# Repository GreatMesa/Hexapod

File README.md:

# Arduino Servo-Powered Hexapod

This hexapod robot is a six-legged walking remote controlled robot that is designed for experimental and recreational purposes.

## Introduction
The 6 legs on the robot are designed to be as stable as possible, this means that the robot doesn't have to spend as much of its power in active stabilization. Besides that, the robot is also made with 3 degree of freedom, which not only model a normal leg of a anthropod but also designates a part of the leg for horizontal, vertical, and extensional movements respectfully. This gives the robot 18 degrees of freedom in total, allowing for more complex walking gait cycles and overall complex movements such as jumping, turning, and speed adjustments. With this alongside potential future sensor integration, I plan to make a robot that can effectively traverse the enviroment around it.

## Manufacturing / Parts (Mechanical Aspect)
For the mechanical aspect of this project I decided to split it into non-custom mechanical part selection, non-custom electrionics selection, custom part manufacturing, and bill of materials. This allows me to better explain each proccess instead of it being all lumped together.

### Non-Custom Mechanical Part Selection
For the servo motors, I want to use the DSServo 35KG servos due to their fast speed and high load tolerance. For the bearings (to reduce the friction on the legs) I utilized the MR148ZZ Deep Groove Ball Bearings due to how small yet efficient they were. For the screws, I selected M3 screws due to being the screw sizes that are standard for the servos I would be using while also being regularly used on 3D prints. Finally, the heated inserts I selected were the M3 3 * 4 * 5 inserts ude to interacting with the M3 screws.

### Non-Custom Electronics Selection
For the Arduino board, the only Arduino that had enough pins for what I wanted to accomplish was the Arduino Mega, although I am pondering a switch to the Arduino Mega Mini to have more space. For the wireless communication protocol I am using 2 NRF24L01+ modules. Besides these 2 sensors I also want to integrate sensors for the robot such as the MPU-6050, and for the RC Transceiver I plan to update this list with the according sensors.

### Custom Part Manufacturing
I plan to use Elegoo Plan PLUS to print out all the custom parts of the hexapod. This filament is good because it is inexpensive for how well it functions. Elegoo Pla Plus gives me the required strength I need for these parts while also allowing me to use a lower than normal infill percentage (15 %). I also plan to use 2 seperate colors (black and red) to not only distinguish between parts, but to also have a cool black spiderman color scheme.

# Component Purchase List

| Item Name | Price (USD) | Quantity | Total Price (USD) | Purchase Link |
|-----------|-------------|----------|--------------------|----------------|
| Dsservo 35KG DS3235 Metal Gear Digital Servo | $8.37 | 20 | $167.67 | [Alibaba](https://www.alibaba.com/product-detail/Dsservo-Waterproof-Servo-High-Torque-35KG_62204650069.html) |
| Chanzon Header Strip for Arduino GPIO 40-pin x 20pcs Female/Male Pins | $9.99 | 1 | $9.99 | [Amazon](https://www.amazon.com/gp/product/B09MY5MJ36) |
| HiLetgo 4pcs NRF24L01+ | $7.89 | 1 | $7.89 | [Amazon](https://www.amazon.com/gp/product/B00LX47OCY) |
| 1600 Pcs M3 Screw Kit, M3 Button Head and Socket Head Screws | $15.00 | 1 | $15.00 | [Amazon](https://www.amazon.com/Takytao-Button-Screws-Machine-Assortment/dp/B0D3TRRKSG) |
| SUNLU TPU 3D Printer Filament 1.75mm | $23.99 | 1 | $23.99 | [Amazon](https://www.amazon.com/SUNLU-TPU-Filament-1-75mm-Flexible/dp/B0BXNWK6NS) |
| ELEGOO PLA Plus Filament 1.75mm Red 1KG | $19.99 | 1 | $19.99 | [Amazon](https://www.amazon.com/ELEGOO-Filament-Dimensional-Accuracy-Compatible/dp/B0BM72LMQH) |
| ELEGOO PLA Plus Filament 1.75mm Black 1KG | $16.99 | 1 | $16.99 | [Amazon](https://www.amazon.com/ELEGOO-Filament-Dimensional-Accuracy-Compatible/dp/B0BM721XHT) |
| MEGA 2560 PRO Embed | $17.99 | 1 | $17.99 | [Amazon](https://www.amazon.com/Songhe-MEGA-2560-ATMEGA2560-Pro-Pinheader/dp/B07TGF9VMQ) |
| BOJACK 3 Values 130 Pcs Solderless Breadboard | $9.99 | 1 | $9.99 | [Amazon](https://www.amazon.com/BOJACK-Values-Solderless-Breadboard-Flexible/dp/B08Y59P6D1) |
| 24 Values Electrolytic Capacitor Assortment Kit | $9.99 | 1 | $9.99 | [Amazon](https://www.amazon.com/ALLECIN-Electrolytic-Capacitor-Assortment-Kit/dp/B0C1VBXCQM) |
| QTEATAK 2Pcs AC 20A/125V 15A/250V DPST 4 Pins 2 Position Switch | $7.99 | 1 | $7.99 | [Amazon](https://www.amazon.com/Position-Rocker-Toggle-Switch-QTEATAK/dp/B08614BYNC) |
| 100Pcs 6x6x5 mm Miniature Micro Momentary Tactile Tact Touch Push Button | $5.99 | 1 | $5.99 | [Amazon](https://www.amazon.com/DAOKI-Miniature-Momentary-Tactile-Quality/dp/B01CGMP9GY) |
| JFtech 5 Pairs Deans T Plug Connector with 100mm 14 AWG Wire | $9.99 | 1 | $9.99 | [Amazon](https://www.amazon.com/gp/product/B09N8WLC2B) |
| HiLetgo ILI9341 2.8" SPI TFT LCD Display Touch Panel 240X320 | $16.39 | 1 | $16.39 | [Amazon](https://www.amazon.com/HiLetgo-240X320-Resolution-Display-ILI9341/dp/B073R7BH1B) |
| HiLetgo 10pcs 4 Channels IIC I2C Logic Level Converter | $7.49 | 1 | $7.49 | [Amazon](https://www.amazon.com/HiLetgo-Channels-Converter-Bi-Directional-3-3V-5V/dp/B07F7W91LC) |

**Total Amount: $347.34**

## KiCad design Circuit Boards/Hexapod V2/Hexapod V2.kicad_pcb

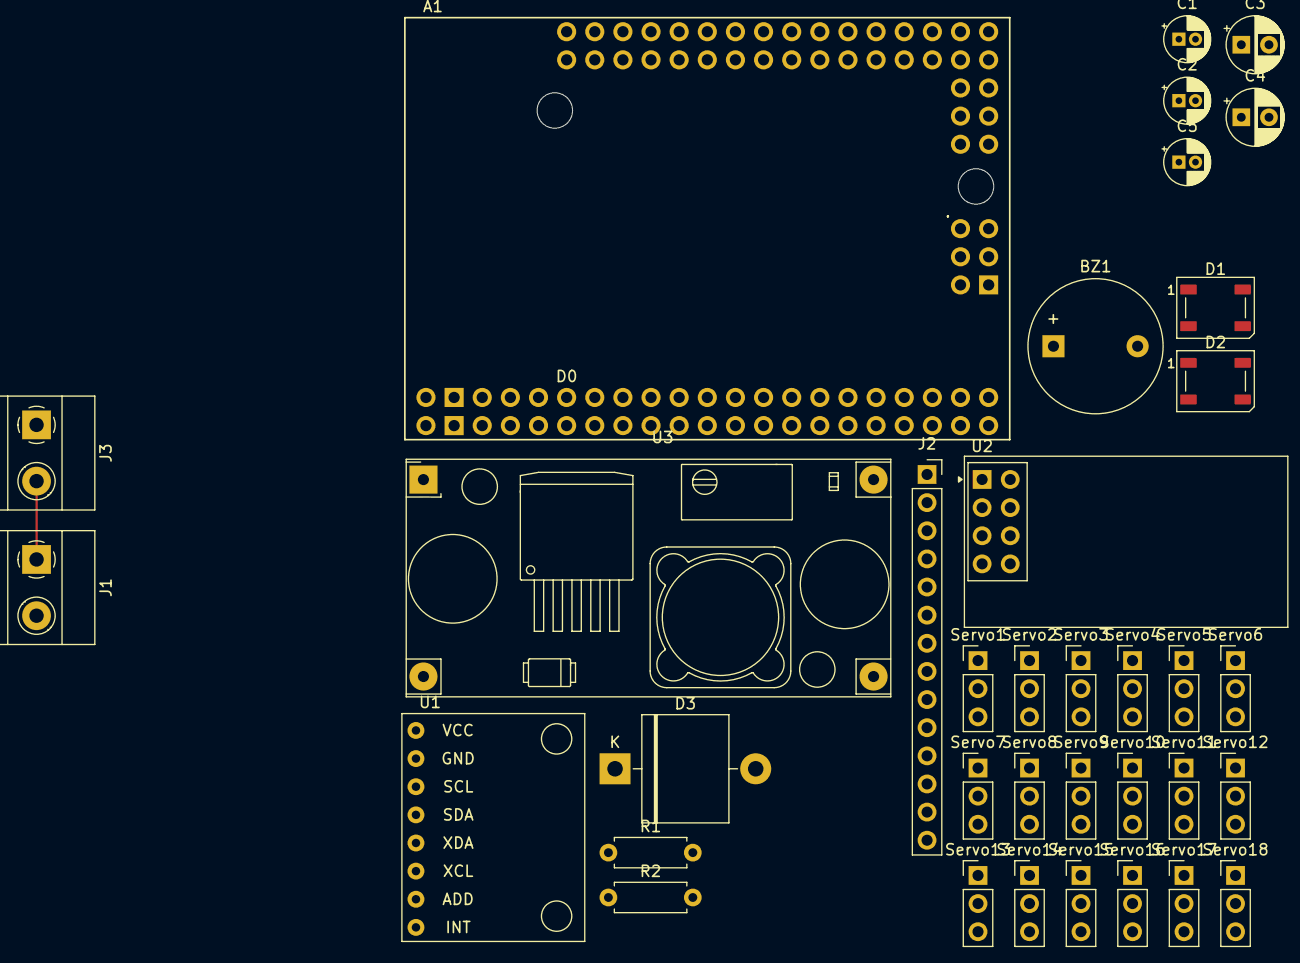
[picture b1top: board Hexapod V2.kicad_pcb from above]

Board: 4 copper layers, 36 parts (0 on the bottom side), 34 nets.

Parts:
A1: Aurduino Mega 2560 Pro; Clone_Mega2560_Pro_Socket
BZ1: Buzzer; Buzzer_12x9.5RM7.6
C1, C2: 0.1μF; CP_Radial_D4.0mm_P1.50mm
C3, C4: 100μF; CP_Radial_D5.0mm_P2.50mm
C5: 22μF; CP_Radial_D4.0mm_P1.50mm
D1, D2: WS2812B; LED_WS2812B_PLCC4_5.0x5.0mm_P3.2mm
D3: D; D_5KP_P12.70mm_Horizontal
J1: Battery; TerminalBlock_Phoenix_MKDS-1,5-2-5.08_1x02_P5.08mm_Horizont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
J2: Conn_01x14_Pin; PinSocket_1x14_P2.54mm_Vertical
J3: Switch; TerminalBlock_Phoenix_MKDS-1,5-2-5.08_1x02_P5.08mm_Horizont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
R1: 10kΩ; R_Axial_DIN0207_L6.3mm_D2.5mm_P7.62mm_Horizontal
R2: 20kΩ; R_Axial_DIN0207_L6.3mm_D2.5mm_P7.62mm_Horizontal
Servo1, Servo2, Servo3, Servo4, Servo5, Servo6, Servo7, Servo8, Servo9, Servo10, Servo11, Servo12, Servo13, Servo14, Servo15, Servo16, Servo17, Servo18: Conn_01x03_Pin; PinHeader_1x03_P2.54mm_Vertical
U1: MPU6050; module_mpu6050
U2: NRF24L01_Breakout; nRF24L01_Breakout
U3: Buck Converter; YAAJ_DCDC_StepDown_LM2596

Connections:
+3.3V: A1.3V31 (3.3V), A1.3V32 (3.3V), U1.1 (VCC)
+5V: A1.5V1 (5V), A1.5V3 (5V), C1.1, C2.1, D1.1 (VDD), D2.1 (VDD), J2.1
A1: R1.1, R2.1
A2: A1.A2, BZ1.1 (+)
CSN: A1.D53 (D53_CS), U2.4 (~CSN)
GND: A1.GND1 (GND), A1.GND2 (GND), BZ1.2 (-), C1.2, C2.2, C3.2, C4.2, C5.2, D1.3 (VSS), D2.3 (VSS), D3.2 (A), J2.2, R1.2, Servo1.1, Servo2.1, Servo3.1, Servo4.1, Servo5.1, Servo6.1, Servo7.1, Servo8.1, Servo9.1, Servo10.1, Servo11.1, Servo12.1, Servo13.1, Servo14.1, Servo15.1, Servo16.1, Servo17.1, Servo18.1, U1.2 (GND), U2.1 (GND), U3.1 (Vin)
MISO: A1.D50 (D50_MISO), J2.6, J2.12, U2.7 (MISO)
MOSI: A1.D51 (D51_MOSI), J2.9, J2.13, U2.6 (MOSI)
unnamed: J1.1, J3.2
unnamed: J1.2, U3.3 (GND)
unnamed: J3.1, U3.4 (Vout)
unnamed: C5.1, U2.2 (VCC)
S1: A1.D7, Servo1.3
S2: A1.D9, Servo2.3
S3: A1.D11, Servo3.3
S4: A1.D13, Servo4.3
S5: A1.D23, Servo5.3
S6: A1.D25, Servo6.3
S7: A1.D27, Servo7.3
S8: A1.D29, Servo8.3
S9: A1.D31, Servo9.3
S10: A1.D33, Servo10.3
S11: A1.D35, Servo11.3
S12: A1.D37, Servo12.3
S13: A1.D39, Servo13.3
S14: A1.D41, Servo14.3
S15: A1.D43, Servo15.3
S16: A1.D45, Servo16.3
S17: A1.D47, Servo17.3
S18: A1.D49, Servo18.3
SCK: A1.D52 (D52_SCK), J2.7, J2.10, U2.5 (SCK)
SCL: A1.D21 (D21/SCL), U1.3 (SCL)
SDA: A1.D20 (D20/SDA), U1.4 (SDA)
VIN: A1.VIN1 (VIN), A1.VIN2 (VIN), C3.1, C4.1, D3.1 (K), R2.2, Servo1.2, Servo2.2, Servo3.2, Servo4.2, Servo5.2, Servo6.2, Servo7.2, Servo8.2, Servo9.2, Servo10.2, Servo11.2, Servo12.2, Servo13.2, Servo14.2, Servo15.2, Servo16.2, Servo17.2, Servo18.2, U3.2 (GND)

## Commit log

2025-06-17 WIP: Save progress before rebase
2025-06-17 Added Images
2025-06-19 Started Journal + Hexapod V2 PCB
2025-06-20 Updated JOURNAL.md
2025-06-20 Updated Bill of Materials
2025-06-23 added new stuff
2025-06-25 Started Firmware + Continued PCB
2025-06-25 Now Firmware is updated
